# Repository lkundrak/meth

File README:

This is my attempt at PCB design in KiCad.

A board with ATMEGA32, an ethernet conntroller, SD card slot, some LEDs, 
buttons and GPIO connectors.

I've not tried if it works at all yet.

Licensed under the terms of CC0:
https://creativecommons.org/publicdomain/zero/1.0/legalcode

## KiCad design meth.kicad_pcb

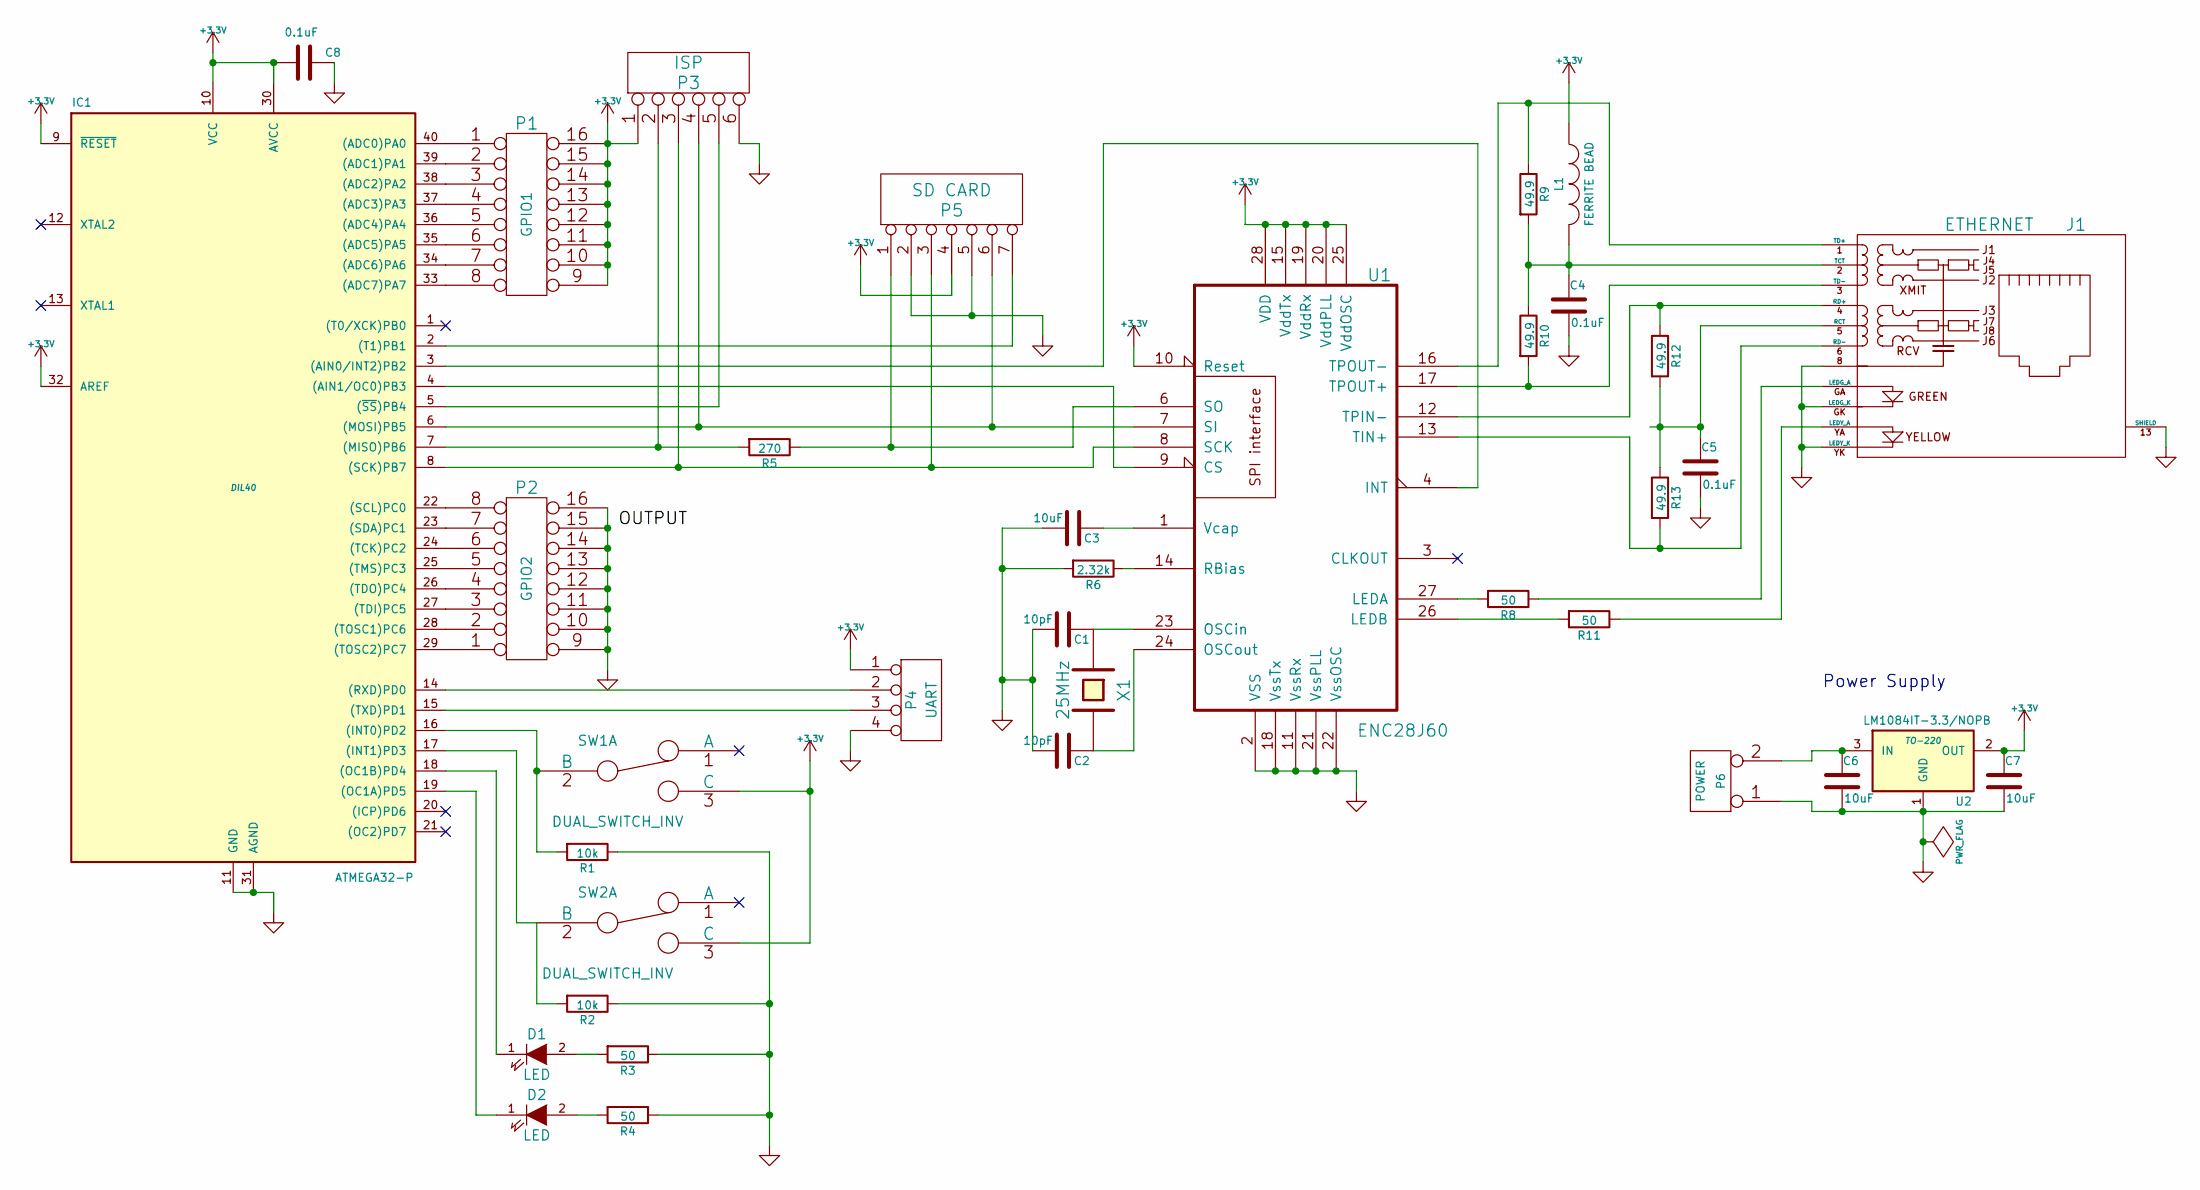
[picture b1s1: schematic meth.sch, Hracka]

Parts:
C1, C2: 10pF
C3, C6, C7: 10uF
C4, C5, C8: 0.1uF
D1, D2: LED
IC1: ATMEGA32-P; DIL40
J1: ETHERNET
L1: FERRITE BEAD
P1: GPIO1
P2: GPIO2
P3: ISP
P4: UART
P5: SD CARD
P6: POWER
R1, R2: 10k
R3, R4, R8, R11: 50
R5: 270
R6: 2.32k
R9, R10, R12, R13: 49.9
SW1, SW2: DUAL_SWITCH_INV
U1: ENC28J60
U2: LM1084IT-3.3/NOPB; TO-220
X1: 25MHz

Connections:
+3.3V: C7.1, C8.2, IC1.9 (~RESET), IC1.10 (VCC), IC1.30 (AVCC), IC1.32 (AREF), L1.1, P1.9, P1.10, P1.11, P1.12, P1.13, P1.14, P1.15, P1.16, P3.1, P4.1, P5.4, SW1.3 (C), SW2.3 (C), U1.10 (Reset), U1.15 (VddTx), U1.19 (VddRx), U1.20 (VddPLL), U1.25 (VddOSC), U1.28 (VDD), U2.2 (OUT)
GND: C1.2, C2.2, C3.2, C4.2, C5.2, C6.2, C7.2, C8.1, IC1.11 (GND), IC1.31 (AGND), J1.8, J1.13 (SHIELD), J1.GK (LEDG_K), J1.YK (LEDY_K), P2.9, P2.10, P2.11, P2.12, P2.13, P2.14, P2.15, P2.16, P3.6, P4.4, P5.2, P5.5, P6.1, R1.1, R2.1, R3.1, R4.1, R6.2, U1.2 (VSS), U1.11 (VssRx), U1.18 (VssTx), U1.21 (VssPLL), U1.22 (VssOSC), U2.1 (GND)
unnamed: C1.1, U1.23 (OSCin), X1.1
unnamed: C2.1, U1.24 (OSCout), X1.2
unnamed: C3.1, U1.1 (Vcap)
unnamed: C4.1, J1.2 (TCT), L1.2, R9.2, R10.1
unnamed: C5.1, J1.5 (RCT), R12.2, R13.1
unnamed: C6.1, P6.2 (PM), U2.3 (IN)
unnamed: D1.1 (K), IC1.18 ((OC1B)PD4)
unnamed: D1.2 (A), R3.2
unnamed: D2.1 (K), IC1.19 ((OC1A)PD5)
unnamed: D2.2 (A), R4.2
unnamed: IC1.2 ((T1)PB1), P5.7
unnamed: IC1.3 ((AIN0/INT2)PB2), U1.4 (INT)
unnamed: IC1.4 ((AIN1/OC0)PB3), U1.9 (CS)
unnamed: IC1.5 ((~SS~)PB4), P3.5
unnamed: IC1.6 ((MOSI)PB5), P3.4, P5.6, U1.7 (SI)
unnamed: IC1.7 ((MISO)PB6), P3.2, R5.2
unnamed: IC1.8 ((SCK)PB7), P3.3, P5.3, U1.8 (SCK)
unnamed: IC1.14 ((RXD)PD0), P4.2
unnamed: IC1.15 ((TXD)PD1), P4.3
unnamed: IC1.16 ((INT0)PD2), R1.2, SW1.2 (B)
unnamed: IC1.17 ((INT1)PD3), R2.2, SW2.2 (B)
unnamed: IC1.22 ((SCL)PC0), P2.8
unnamed: IC1.23 ((SDA)PC1), P2.7
unnamed: IC1.24 ((TCK)PC2), P2.6
unnamed: IC1.25 ((TMS)PC3), P2.5
unnamed: IC1.26 ((TDO)PC4), P2.4
unnamed: IC1.27 ((TDI)PC5), P2.3
unnamed: IC1.28 ((TOSC1)PC6), P2.2
unnamed: IC1.29 ((TOSC2)PC7), P2.1
unnamed: IC1.33 ((ADC7)PA7), P1.8
unnamed: IC1.34 ((ADC6)PA6), P1.7
unnamed: IC1.35 ((ADC5)PA5), P1.6
unnamed: IC1.36 ((ADC4)PA4), P1.5
unnamed: IC1.37 ((ADC3)PA3), P1.4
unnamed: IC1.38 ((ADC2)PA2), P1.3
unnamed: IC1.39 ((ADC1)PA1), P1.2
unnamed: IC1.40 ((ADC0)PA0), P1.1
unnamed: J1.1 (TD+), R9.1, U1.16 (TPOUT-)
unnamed: J1.3 (TD-), R10.2, U1.17 (TPOUT+)
unnamed: J1.4 (RD+), R12.1, U1.12 (TPIN-)
unnamed: J1.6 (RD-), R13.2, U1.13 (TIN+)
unnamed: J1.GA (LEDG_A), R8.1
unnamed: J1.YA (LEDY_A), R11.1
unnamed: P5.1, R5.1, U1.6 (SO)
unnamed: R6.1, U1.14 (RBias)
unnamed: R8.2, U1.27 (LEDA)
unnamed: R11.2, U1.26 (LEDB)

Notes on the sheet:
Power Supply

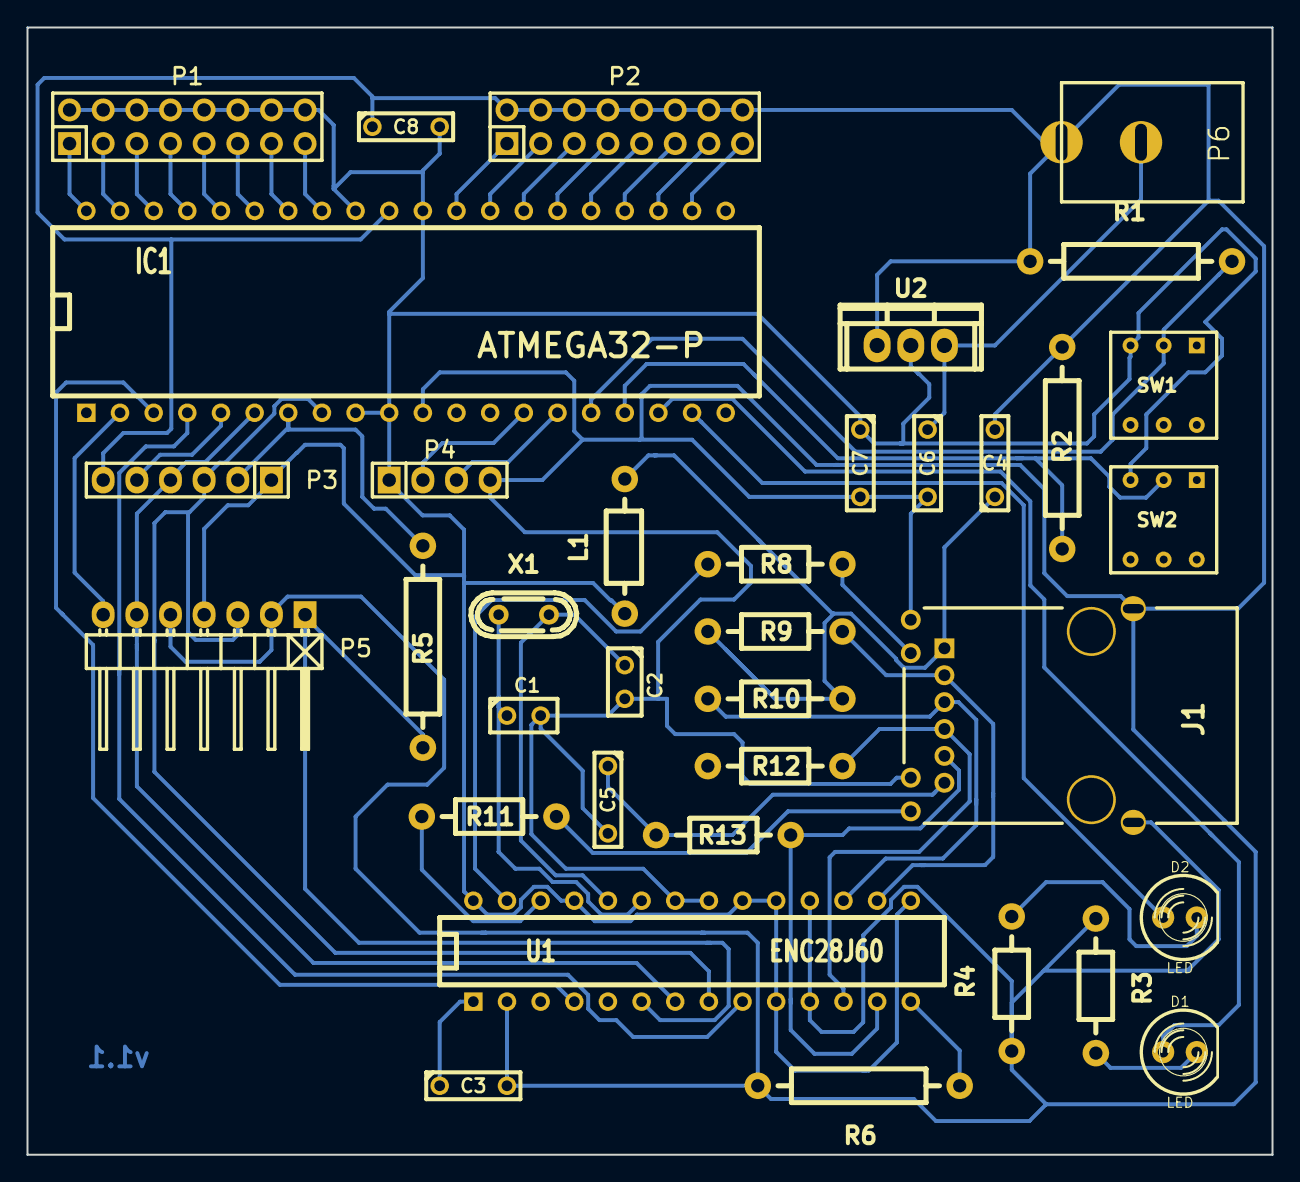
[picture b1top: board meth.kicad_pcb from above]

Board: 2 copper layers, 94.0 x 85.1 mm, 36 parts (0 on the bottom side), 49 nets.

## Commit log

2015-03-29 Add schema
2015-03-29 Add library cache
2015-03-29 Add netlist
2015-03-29 Add board
2015-03-29 Add footprint library
2015-03-29 Add gitignore
2015-03-29 Add README
2015-08-03 newer kicad
2015-08-03 Reroute
2015-08-03 Optimize
2015-08-03 Fill
2015-08-04 Some rerouting
2015-08-04 Fixups
